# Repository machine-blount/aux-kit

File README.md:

# aux-kit
***Your new auxiliary framework***

Aux-kit is designed to be an all in one auxiliary/supplementary solution for any electric-powered solar car teams competing in the National Solar Car Challenge. In its current version It is designed as a Pi-HAT which connects to multiple expansion boards for quick iteration on separate parts of the system. 

All of the boards are only double sided so if you have an iso-mill or a fiber laser you can cook yourself up an aux-kit quickly for cheap. Most of the components are common but you may have to look out for:

- CAT24C256(EEPROM)
- DMMT5401-7(PNP Transistor Pair), 
- DMG2305UX(P-Channel Enhancement Mode MOSFET), 
- LM2596(Step-Down Converter).

## v1.0.0 Feature List
- Horn Control 
- Left Turn Signals  
- Right Turn Signals
- Hazards
- Brake Lights
- Battery Monitor 
- On-Board 12V-5V Step-Down Converter

Currently aux-kit only supports the basic supplementary/auxiliary requirements for the ESPV division but this is why the board leaves you with ~35mm x 22mm of square free real estate for any additional hardware. Additionally aux-kit has solder jumpers on the underside of the board which allow you to choose whether to control certain features programmatically through the Pi directly, or if you just want the integrated analog control to handle it for you. 

Initially I had designed aux-kit for my own team but because of the collaborative environment inside of the NSCC I had second thoughts and decided to open source the project for any another team to contribute.

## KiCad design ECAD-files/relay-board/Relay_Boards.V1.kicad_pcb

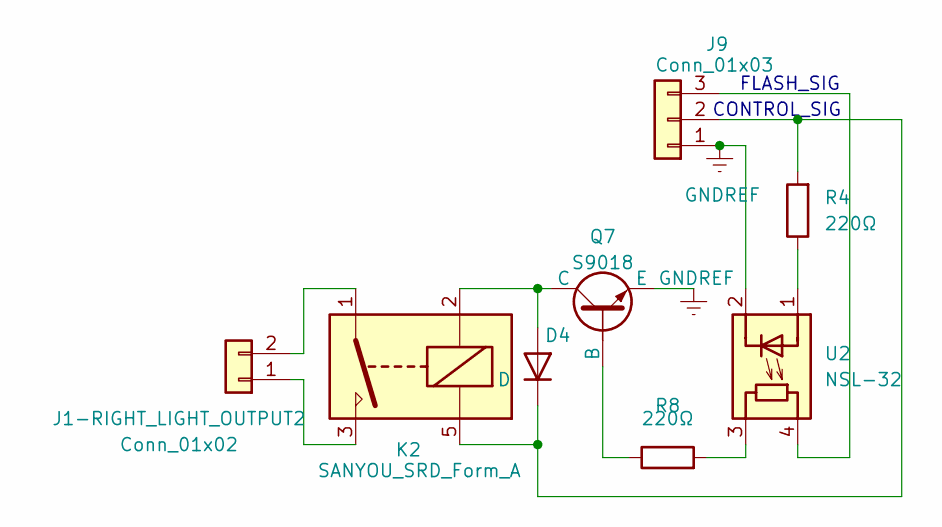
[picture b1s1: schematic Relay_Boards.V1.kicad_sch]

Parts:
D4: D; D_A-405_P7.62mm_Horizontal
J1-RIGHT_LIGHT_OUTPUT2: Conn_01x02; TerminalBlock_bornier-2_P5.08mm
J9: Conn_01x03; JST_XH_B3B-XH-A_1x03_P2.50mm_Vertical
K2: SANYOU_SRD_Form_A; Relay_SPDT_SANYOU_SRD_Series_Form_C
Q7: S9018; PinHeader_1x03_P2.54mm_Vertical
R4, R8: 220Ω; R_Axial_DIN0207_L6.3mm_D2.5mm_P10.16mm_Horizontal
U2: NSL-32; Diode_Bridge_DIP-4_W5.08mm_P2.54mm

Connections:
GNDREF: J9.1, Q7.3 (E), U2.2 (K)
unnamed: D4.2 (A), K2.2, Q7.1 (C)
unnamed: D4.1 (K), J9.2, K2.5, R4.2
unnamed: J1-RIGHT_LIGHT_OUTPUT2.1, K2.3
unnamed: J1-RIGHT_LIGHT_OUTPUT2.2, K2.1
unnamed: J9.3, U2.4 (R)
unnamed: Q7.2 (B), R8.1
unnamed: R8.2, U2.3 (R)
unnamed: R4.1, U2.1 (A)

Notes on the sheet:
FLASH_SIG
CONTROL_SIG

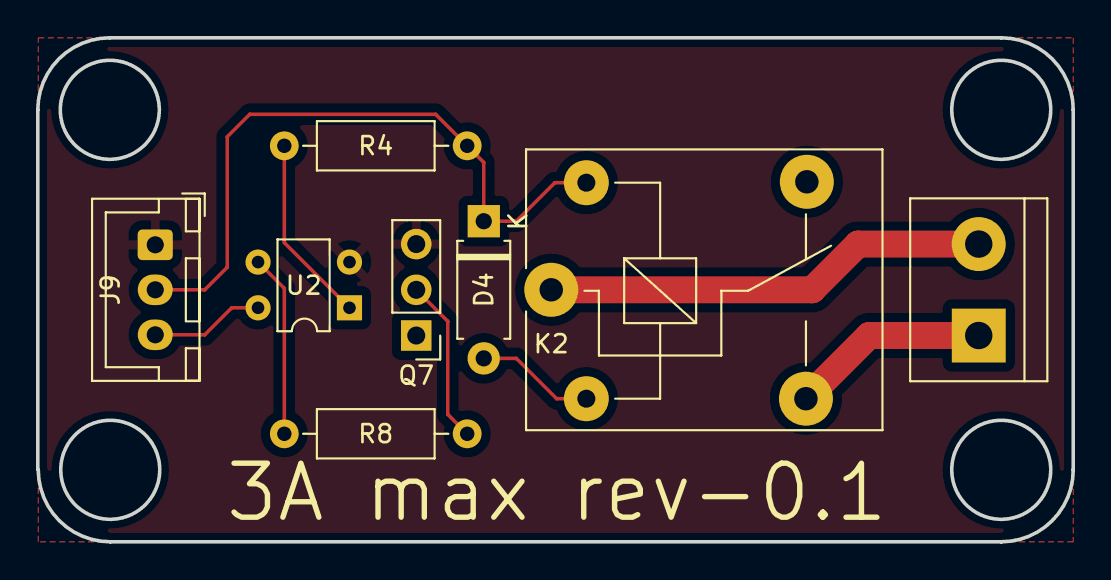
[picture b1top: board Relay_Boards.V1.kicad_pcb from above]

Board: 2 copper layers, 57.5 x 28.0 mm, 8 parts (0 on the bottom side), 9 nets.

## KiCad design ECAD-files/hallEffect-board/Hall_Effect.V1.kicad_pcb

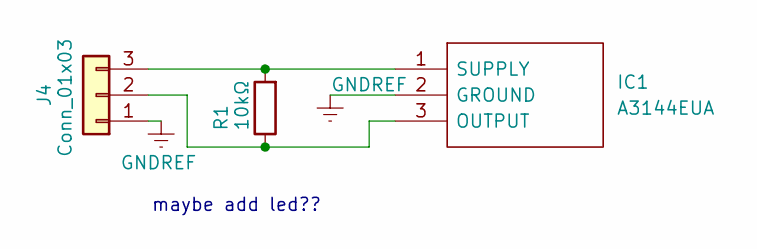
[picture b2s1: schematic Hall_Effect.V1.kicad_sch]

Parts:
IC1: A3144EUA; PinHeader_1x03_P1.27mm_Vertical; Manufacturer_Part_Number A3144EUA
J4: Conn_01x03; JST_XH_B3B-XH-A_1x03_P2.50mm_Vertical
R1: 10kΩ; R_Axial_DIN0207_L6.3mm_D2.5mm_P10.16mm_Horizontal

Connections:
GNDREF: IC1.2 (GROUND), J4.1
unnamed: IC1.3 (OUTPUT), J4.2, R1.1
unnamed: IC1.1 (SUPPLY), J4.3, R1.2

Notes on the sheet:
maybe add led??

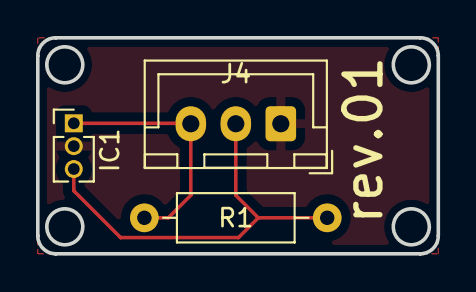
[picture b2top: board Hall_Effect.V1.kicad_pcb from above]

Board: 2 copper layers, 22.2 x 12.0 mm, 3 parts (0 on the bottom side), 3 nets.

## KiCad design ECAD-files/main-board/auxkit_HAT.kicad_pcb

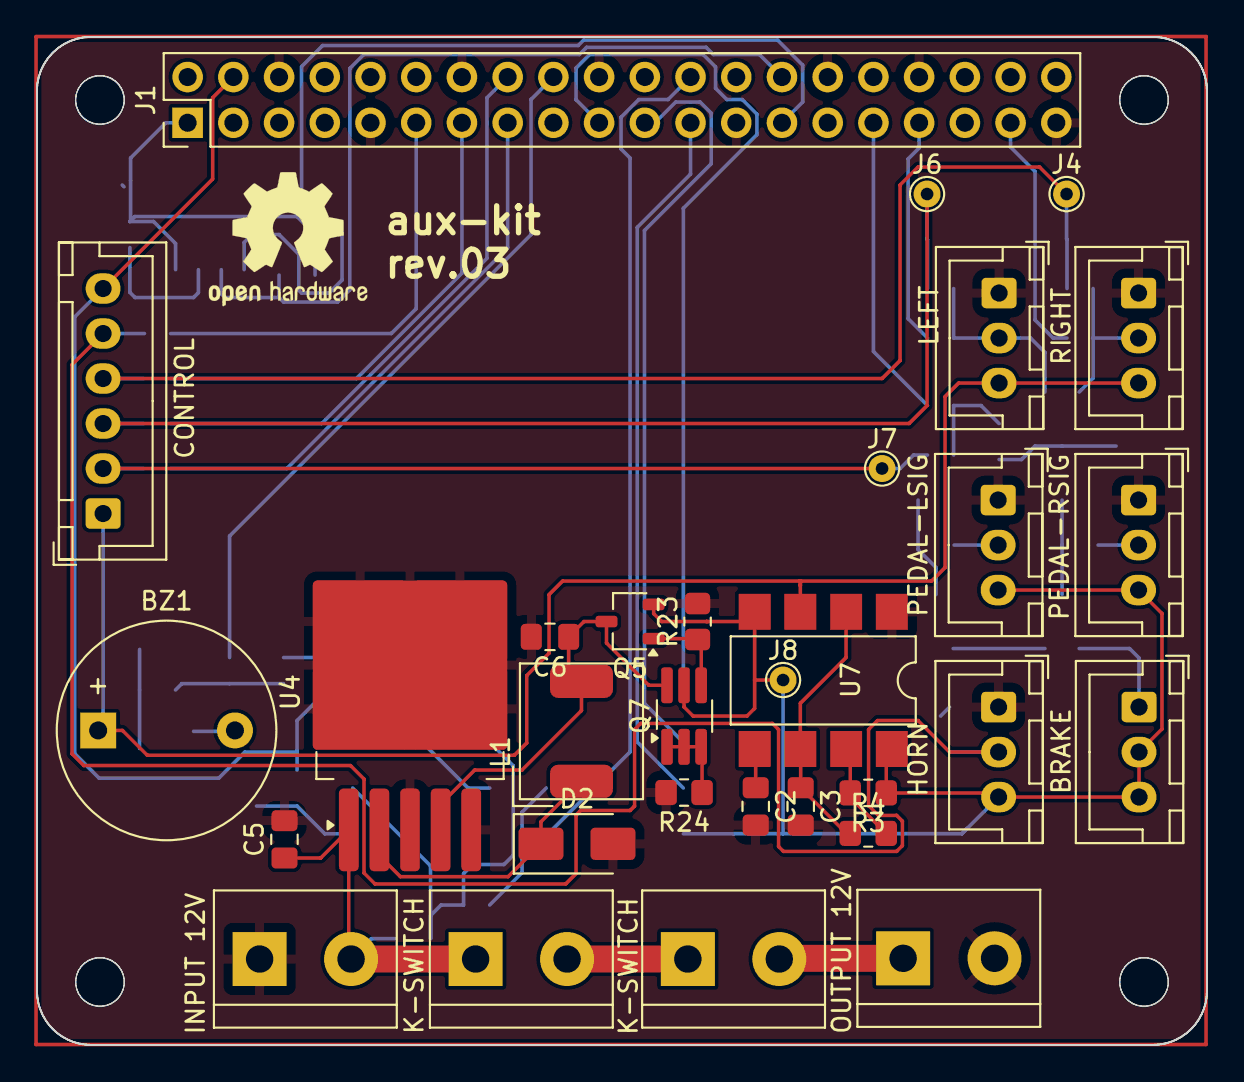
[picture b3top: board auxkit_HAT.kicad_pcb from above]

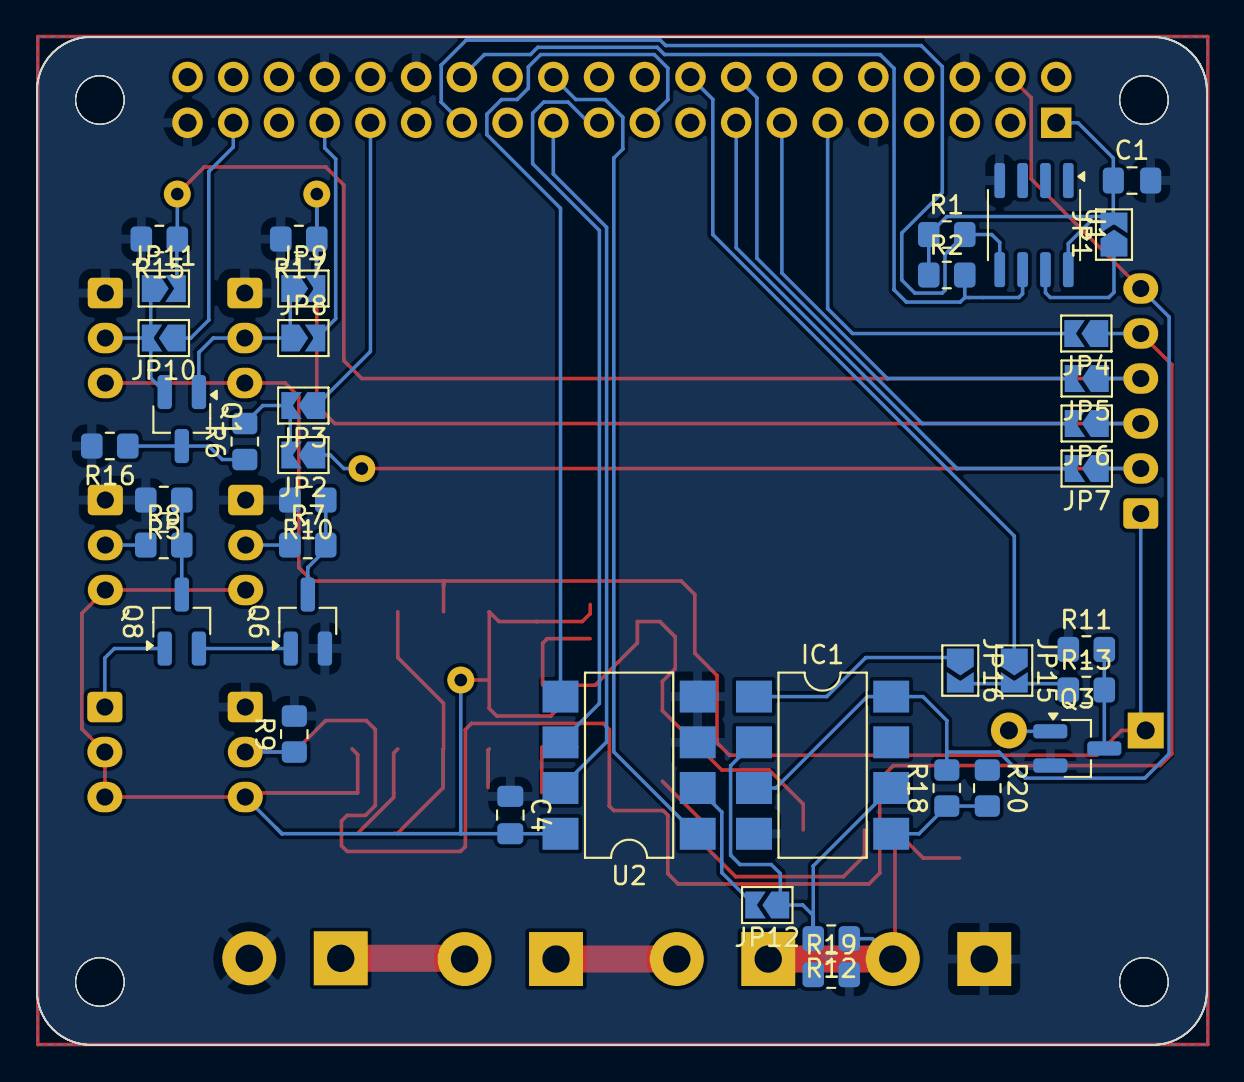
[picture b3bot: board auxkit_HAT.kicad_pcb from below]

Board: 2 copper layers, 65.0 x 56.0 mm, 79 parts (40 on the bottom side), 51 nets.

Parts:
BRAKE: BRAKE_LIGHT; JST_XH_B3B-XH-A_1x03_P2.50mm_Vertical
BZ1: Buzzer; Buzzer_12x9.5RM7.6
C1: 100n; C_0805_2012Metric_Pad1.18x1.45mm_HandSolder
C2, C4: 0.1µF; C_0805_2012Metric_Pad1.18x1.45mm_HandSolder
C3: 1µF; C_0805_2012Metric_Pad1.18x1.45mm_HandSolder
C5: 680uF; C_0805_2012Metric_Pad1.18x1.45mm_HandSolder
C6: 330uF; C_0805_2012Metric_Pad1.18x1.45mm_HandSolder
CONTROL: DRIVER_CNTRL; JST_XH_B6B-XH-A_1x06_P2.50mm_Vertical
D2: SS34; D_SMA
HORN: HORN; JST_XH_B3B-XH-A_1x03_P2.50mm_Vertical
IC1: LM393N; SMDIP-8_W7.62mm
INPUT 12V: Conn_01x02; TerminalBlock_bornier-2_P5.08mm
J1: GPIO; PinHeader_2x20_P2.54mm_Vertical
J4, J6, J7, J8: Conn_01x01; TestPoint_THTPad_D1.5mm_Drill0.7mm
JP1: ID_WP; SolderJumper-2_P1.3mm_Open_TrianglePad1.0x1.5mm
JP2, JP3, JP4, JP5, JP6, JP7, JP8, JP9, JP10, JP11, JP12, JP15, JP16: SolderJumper_2_Open; SolderJumper-2_P1.3mm_Open_TrianglePad1.0x1.5mm
K-SWITCH: Conn_01x02; TerminalBlock_bornier-2_P5.08mm
K-SWITCH#2: Conn_01x02; TerminalBlock_bornier-2_P5.08mm
L1: 33uH; L_AVX_LMLP07A7
LEFT: LEFT_TURN; JST_XH_B3B-XH-A_1x03_P2.50mm_Vertical
MH1, MH1#2, MH2, MH2#2, MH3, MH3#2, MH4, MH4#2: MountingHole_2.7mm_M2.5
OUTPUT 12V: Conn_01x02; TerminalBlock_bornier-2_P5.08mm
PEDAL-LSIG: LEFT_TURN; JST_XH_B3B-XH-A_1x03_P2.50mm_Vertical
PEDAL-RSIG: RIGHT_TURN; JST_XH_B3B-XH-A_1x03_P2.50mm_Vertical
Q1, Q3, Q6, Q8: NPN; SOT-23_Handsoldering
Q5: DMG2305UX; TSOT-23
Q7: DMMT5401-7; TSOT-23-6_HandSoldering
R1, R2: 3.9k; R_0805_2012Metric_Pad1.20x1.40mm_HandSolder
R3: ?Ω; R_0805_2012Metric_Pad1.20x1.40mm_HandSolder
R4: 1kΩ; R_0805_2012Metric_Pad1.20x1.40mm_HandSolder
R5, R10: 4.7kΩ; R_0805_2012Metric_Pad1.20x1.40mm_HandSolder
R6, R7, R8, R9, R11, R13, R15, R16, R17: R; R_0805_2012Metric_Pad1.20x1.40mm_HandSolder
R12: 6.8K; R_0805_2012Metric_Pad1.20x1.40mm_HandSolder
R18: 220Ω; R_0805_2012Metric_Pad1.20x1.40mm_HandSolder
R19: 4.7K; R_0805_2012Metric_Pad1.20x1.40mm_HandSolder
R20: 2.2K; R_0805_2012Metric_Pad1.20x1.40mm_HandSolder
R23: 47K; R_0805_2012Metric_Pad1.20x1.40mm_HandSolder
R24: 10K; R_0805_2012Metric_Pad1.20x1.40mm_HandSolder
RIGHT: RIGHT_TURN; JST_XH_B3B-XH-A_1x03_P2.50mm_Vertical
U1: CAT24C256; SOIC-8_3.9x4.9mm_P1.27mm
U2: MCP3002; SMDIP-8_W7.62mm
U4: LM2596S-5; TO-263-5_TabPin3
U7: NE555P; SMDIP-8_W7.62mm

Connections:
+3V3: C1.1, J1.1, J1.17, JP1.2 (B), R1.1, R2.1, U1.8 (VCC)
+5V: BRAKE.2, BRAKE.3, C4.2, CONTROL.6, HORN.3, IC1.3 (IN1(+)), IC1.8 (VCC), J1.4, J8.1, PEDAL-LSIG.3, PEDAL-RSIG.3, Q5.2 (S), Q7.5 (E2), R3.1, R18.2, U2.8 (VDD/VREF), U7.4 (R), U7.8 (VCC)
/ANO_ALARM: IC1.1 (OUTPUT1), JP16.1 (A)
/DIGI-ALARM24: J1.18, JP15.1 (A)
/FLASH_GEN: BZ1.1 (+), CONTROL.1, LEFT.3, RIGHT.3, U7.3 (Q)
/GPIO8/SPI0.CE0: J1.24, U2.1 (~CS/SHDN)
/GPIO9/SPI0.MISO: J1.21, U2.6 (DOUT)
/GPIO10/SPI0.MOSI: J1.19, U2.5 (DIN)
/GPIO11/SPI0.SCLK: J1.23, U2.7 (CLK)
/HAZARD-GPIO23: J1.15, JP7.1 (A)
/HAZARD-SIG6: J1.31, JP3.1 (A)
/HAZARD_CNTRL: CONTROL.2, J7.1, JP2.1 (A), JP7.2 (B)
/HORN-CTRL: HORN.2, R9.1
/HORN-GPIO17: J1.11, JP4.2 (B)
/HORN_CTRL: CONTROL.5, JP4.1 (A)
/ID_SCL: J1.28, R2.2, U1.6 (SCL)
/ID_SDA: J1.27, R1.2, U1.5 (SDA)
/LEFT-GPIO22: J1.16, JP6.2 (B)
/LEFT-SIG13: J1.33, JP8.2 (B)
/LEFT_CNTRL: CONTROL.3, J6.1, JP6.1 (A), JP9.2 (B), R17.1
/LEFT_PEDAL_SENSOR: Q6.2 (B), R7.1, R10.1
/RIGHT-GPIO27: J1.13, JP5.2 (B)
/RIGHT-SIG26: J1.37, JP10.1 (A)
/RIGHT_CNTRL: CONTROL.4, J4.1, JP5.1 (A), JP11.2 (B), R15.1
/RIGHT_PEDAL_SENSOR: Q8.2 (B), R5.1, R8.2
/~4.5: IC1.5 (IN2(+)), R18.1, R20.2
GNDREF: C1.2, C2.2, C3.2, C4.1, C5.2, C6.2, D2.2 (A), HORN.1, IC1.4 (GND), INPUT 12V.1, J1.6, J1.9, J1.14, J1.20, J1.25, J1.30, J1.34, J1.39, LEFT.1, OUTPUT 12V.1, PEDAL-LSIG.1, PEDAL-RSIG.1, Q3.3 (E), Q6.3 (E), R5.2, R9.2, R10.2, R11.1, R15.2, R16.2, R17.2, R19.2, R20.1, R23.2, R24.2, RIGHT.1, U1.4 (GND), U2.3 (CH1), U2.4 (VSS), U4.3 (GND), U4.5 (~ON/OFF), U7.1 (GND)
unnamed: BZ1.2 (-), Q3.1 (C)
unnamed: D2.1 (K), L1.1, U4.2 (OUT)
unnamed: IC1.2 (IN1(-)), IC1.6 (IN2(-)), JP12.1 (A), R12.2, R19.1
unnamed: C5.1, INPUT 12V.2, K-SWITCH#2.1, R12.1, U4.1 (VIN)
unnamed: K-SWITCH.2, OUTPUT 12V.2
unnamed: BRAKE.1, Q8.1 (C)
unnamed: JP8.1 (A), JP9.1 (A), LEFT.2, Q1.1 (C)
unnamed: JP10.2 (B), JP11.1 (A), Q1.3 (E), RIGHT.2
unnamed: PEDAL-RSIG.2, R8.1
unnamed: PEDAL-LSIG.2, R7.2
unnamed: JP1.1 (A), U1.7 (WP)
unnamed: JP2.2 (B), JP3.2 (B), R6.2
unnamed: JP12.2 (B), U2.2 (CH0)
unnamed: JP15.2 (B), JP16.2 (B), R13.1
unnamed: K-SWITCH.1, K-SWITCH#2.2
unnamed: Q1.2 (B), R6.1, R16.1
unnamed: Q3.2 (B), R11.2, R13.2
unnamed: C6.1, L1.2, Q5.3 (D), Q7.6 (E1), U4.4 (FB)
unnamed: Q5.1 (G), Q7.4 (C2), R23.1
unnamed: Q6.1 (C), Q8.3 (E)
unnamed: Q7.1 (C1), Q7.2 (B1), Q7.3 (B2), R24.1
unnamed: C2.1, U7.5 (CV)
unnamed: R3.2, R4.2, U7.7 (DIS)
unnamed: C3.1, R4.1, U7.2 (TR), U7.6 (THR)

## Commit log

2024-12-15 Add files via upload
    aux-kit rev.03 gerbers
2025-01-09 aux-kit readme rundown 1st draft
